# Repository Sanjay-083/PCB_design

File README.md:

View this project on [CADLAB.io](https://cadlab.io/project/29062). 

# PCB_design

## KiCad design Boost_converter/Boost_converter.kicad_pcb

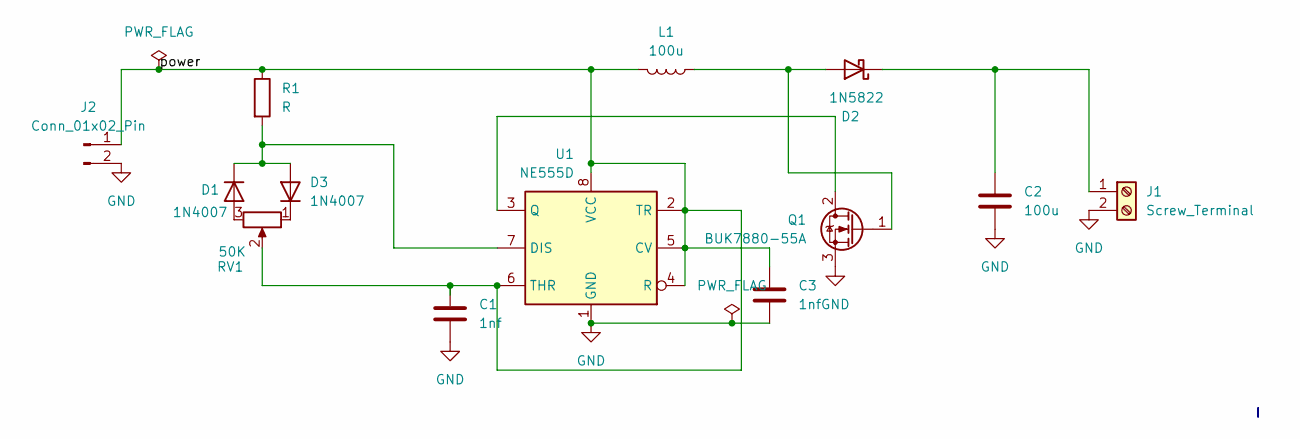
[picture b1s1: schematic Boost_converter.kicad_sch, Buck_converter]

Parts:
C1: 1nf; C_Disc_D10.0mm_W2.5mm_P5.00mm
C2: 100u; C_Radial_D5.0mm_H11.0mm_P2.00mm
C3: 1nf; C_Radial_D5.0mm_H11.0mm_P2.00mm
D1: 1N4007; D_DO-34_SOD68_P7.62mm_Horizontal
D2: 1N5822; D_DO-201AD_P15.24mm_Horizontal
D3: 1N4007; D_DO-41_SOD81_P10.16mm_Horizontal
J1: Screw_Terminal; TerminalBlock_MaiXu_MX126-5.0-02P_1x02_P5.00mm
J2: Conn_01x02_Pin; TerminalBlock_MaiXu_MX126-5.0-02P_1x02_P5.00mm
L1: 100u; L_Radial_D9.5mm_P5.00mm_Fastron_07HVP
Q1: BUK7880-55A; SOT-223-3_TabPin2
R1: R; R_0201_0603Metric_Pad0.64x0.40mm_HandSolder
RV1: 50K; Potentiometer_Bourns_3009P_Horizontal
U1: NE555D; SOIC-8_3.9x4.9mm_P1.27mm

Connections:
GND: C1.2, C2.2, C3.2, J1.2, J2.2, Q1.3 (S), U1.1 (GND)
unnamed: D1.2 (A), RV1.3
unnamed: D1.1 (K), D3.2 (A), R1.2, U1.7 (DIS)
unnamed: D2.2 (A), L1.1, Q1.1 (G)
unnamed: C2.1, D2.1 (K), J1.1
unnamed: D3.1 (K), RV1.1
unnamed: C1.1, C3.1, J2.1, L1.2, R1.1, RV1.2, U1.2 (TR), U1.4 (R), U1.5 (CV), U1.6 (THR), U1.8 (VCC)
unnamed: Q1.2 (D), U1.3 (Q)

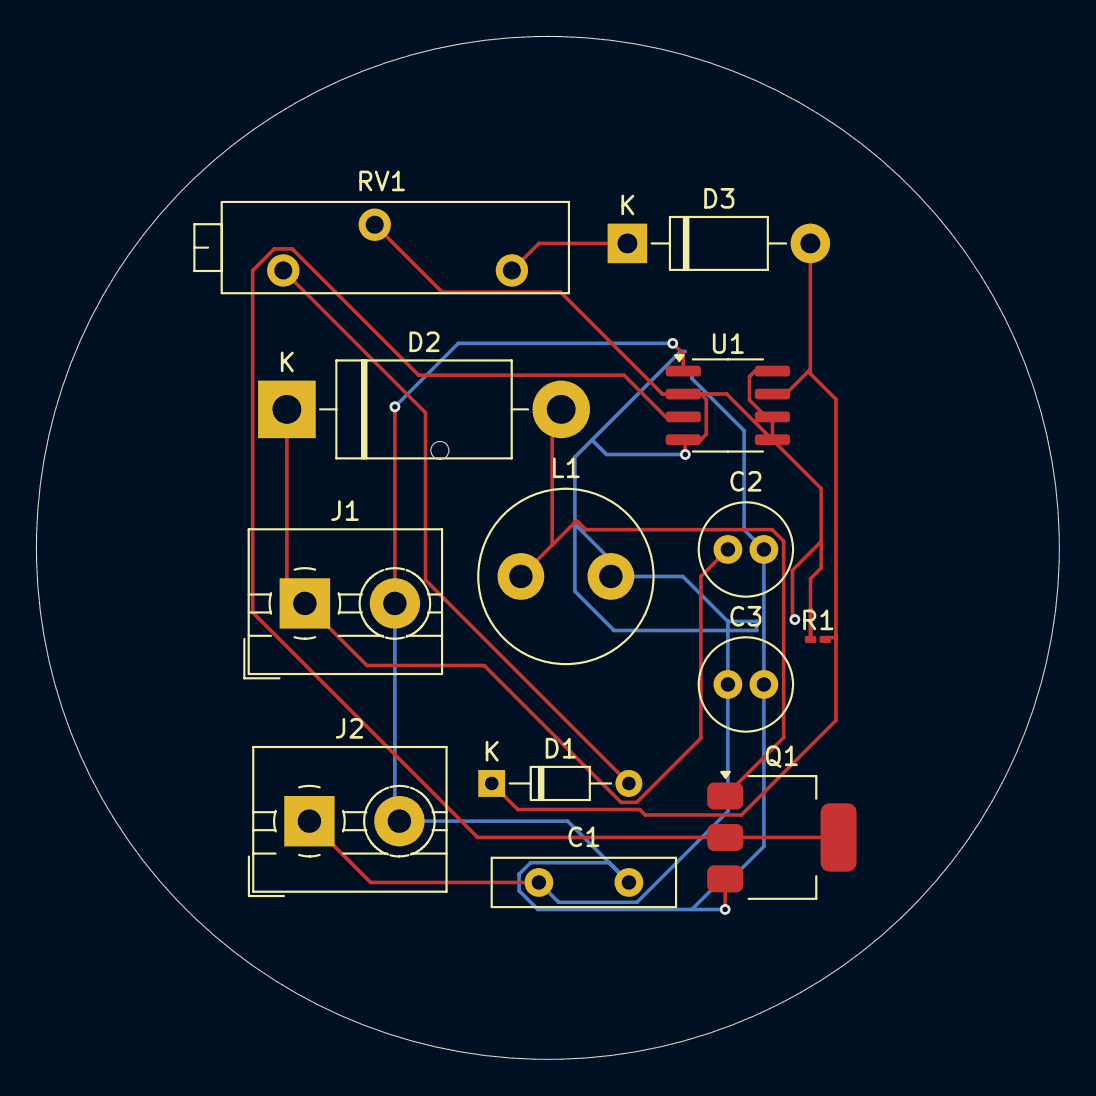
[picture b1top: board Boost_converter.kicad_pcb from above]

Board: 2 copper layers, 56.8 x 56.8 mm, 13 parts (0 on the bottom side), 8 nets.

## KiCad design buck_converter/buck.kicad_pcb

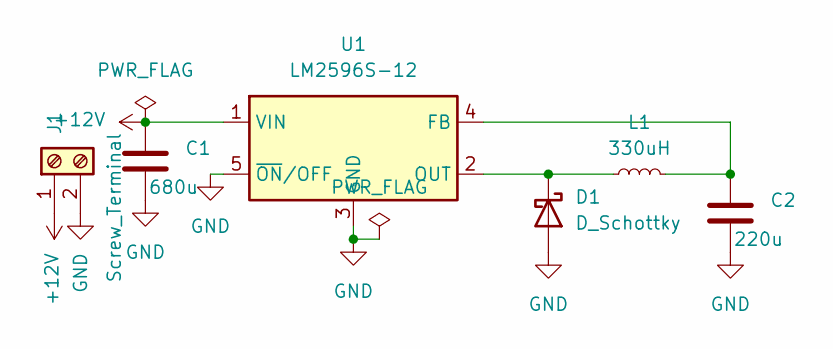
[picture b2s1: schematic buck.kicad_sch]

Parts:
C1: 680u; C_Axial_L5.1mm_D3.1mm_P7.50mm_Horizontal
C2: 220u; C_Axial_L5.1mm_D3.1mm_P12.50mm_Horizontal
D1: D_Schottky; D_0201_0603Metric
J1: Screw_Terminal; Altech_AK300_1x02_P5.00mm_45-Degree
L1: 330uH; L_0402_1005Metric
U1: LM2596S-12; TO-263-5_TabPin3

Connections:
+12V: C1.1, J1.1, U1.1 (VIN)
GND: C1.2, C2.2, D1.2 (A), J1.2, U1.3 (GND), U1.5 (~ON/OFF)
unnamed: D1.1 (K), L1.1, U1.2 (OUT)
unnamed: C2.1, L1.2, U1.4 (FB)

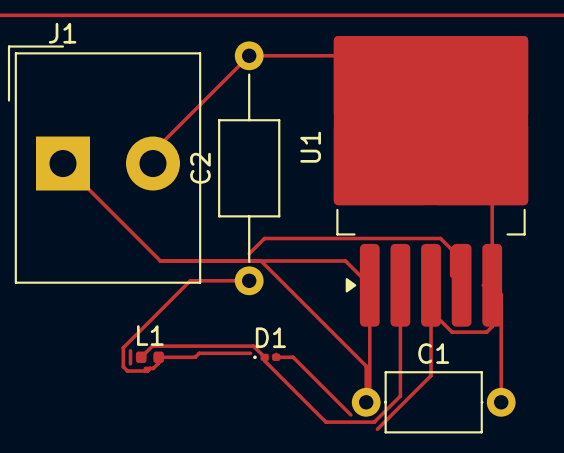
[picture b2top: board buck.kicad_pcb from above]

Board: 2 copper layers, 6 parts (0 on the bottom side), 4 nets.

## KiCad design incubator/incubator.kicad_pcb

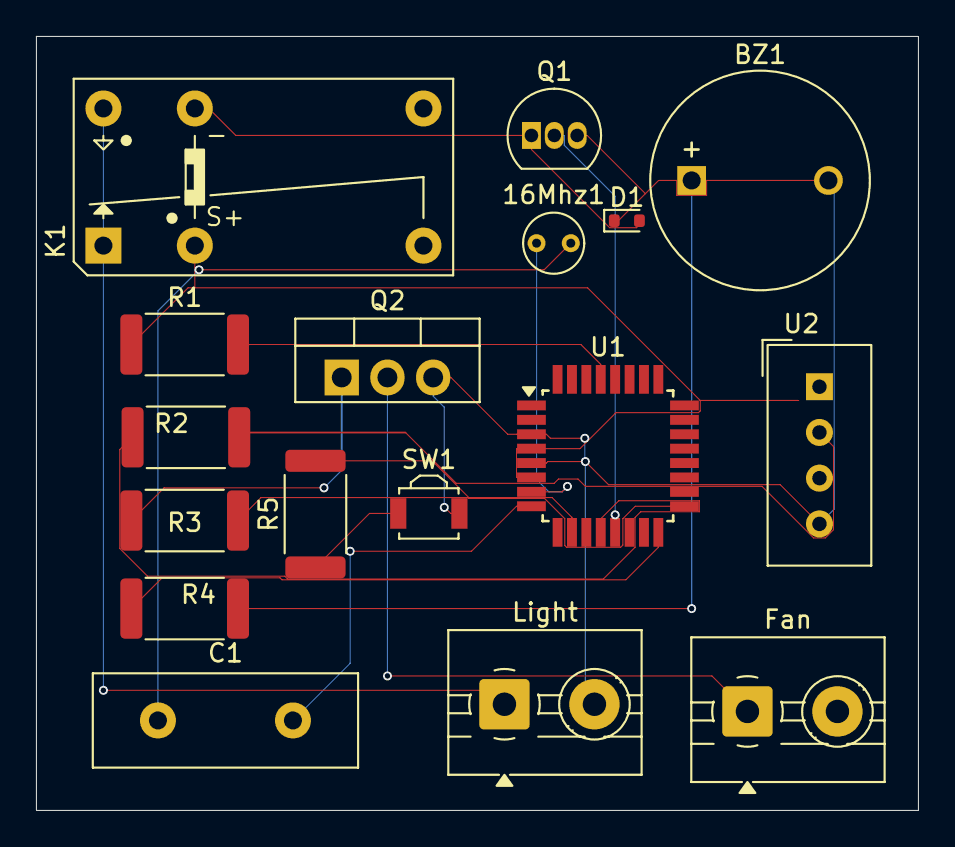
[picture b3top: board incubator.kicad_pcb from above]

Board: 2 copper layers, 49.0 x 43.0 mm, 17 parts (0 on the bottom side), 16 nets.

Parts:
16Mhz1: Crystal; Crystal_C38-LF_D3.0mm_L8.0mm_Vertical
BZ1: Buzzer; MagneticBuzzer_ProSignal_ABI-009-RC
C1: 22pf; C_Disc_D14.5mm_W5.0mm_P7.50mm
D1: 1N4148WT; D_SOD-523
Fan: Fan; TerminalBlock_MaiXu_MX126-5.0-02P_1x02_P5.00mm
K1: Relay_SPDT; Relay_SPDT_Panasonic_DR-L
Light: Light; TerminalBlock_MaiXu_MX126-5.0-02P_1x02_P5.00mm
Q1: BC547; TO-92_Inline
Q2: IRF540N; TO-220-3_Vertical
R1, R3, R5: 10k; R_2512_6332Metric
R2: 4.7K; R_2512_6332Metric
R4: 1k; R_2512_6332Metric
SW1: SW_Push; SW_SPST_B3U-3000P
U1: ATmega8A-A; TQFP-32_7x7mm_P0.8mm
U2: DHT11; Aosong_DHT11_5.5x12.0_P2.54mm

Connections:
unnamed: 16Mhz1.2, BZ1.2 (-), C1.1, D1.1 (K), K1.A1, Light.2, Q1.3 (E), Q2.3 (S), R1.1, SW1.2, U1.3 (GND), U1.4 (VCC), U1.5 (GND), U1.6 (VCC), U2.1 (VDD), U2.4 (GND)
unnamed: BZ1.1 (+), R4.2
unnamed: D1.2 (A), K1.A2, Q1.1 (C)
unnamed: K1.12, K1.14, Light.1
unnamed: Fan.1, Q2.2 (D)
unnamed: Q1.2 (B), U1.13 (PB1)
unnamed: Q2.1 (G), R3.1
unnamed: R5.1, SW1.1
unnamed: R2.1, U1.12 (PB0)
unnamed: R4.1, U1.16 (PB4)
unnamed: R3.2, U1.17 (PB5)
unnamed: 16Mhz1.1, U1.7 (PB6/XTAL1)
unnamed: C1.2, U1.8 (PB7/XTAL2)
unnamed: R1.2, U1.29 (PC6/~RESET)
unnamed: R5.2, U1.10 (PD6)
unnamed: R2.2, U2.2 (DATA)

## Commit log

2025-03-25 assignments updated
2025-03-27 Rename incubator-2025-03-24_200620.zip to incubator
2025-03-27 incubator added
2025-03-28 added
2025-03-28 Backlink to CADLAB.io has been added.
